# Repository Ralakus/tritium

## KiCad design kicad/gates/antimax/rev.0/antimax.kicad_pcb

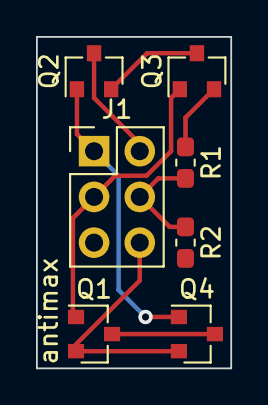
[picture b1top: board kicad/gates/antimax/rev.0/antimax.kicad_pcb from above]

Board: 2 copper layers, 10.8 x 18.4 mm, 7 parts (0 on the bottom side), 8 nets.

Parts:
J1: Conn_02x03_Odd_Even; PinHeader_2x03_P2.54mm_Vertical
Q1, Q4: 2N7002; SOT-23
Q2, Q3: BSS84; SOT-23
R1, R2: 12k; R_0603_1608Metric_Pad1.05x0.95mm_HandSolder

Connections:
A: J1.1, Q2.1, Q4.1
B: J1.3, Q1.1, Q3.1
unnamed: Q1.3, Q4.3, R2.2
unnamed: Q2.2, Q3.3
unnamed: Q3.2, R1.1
Out: J1.4, R1.2, R2.1
Vdd: J1.2, Q2.3
Vss: J1.6, Q1.2, Q4.2

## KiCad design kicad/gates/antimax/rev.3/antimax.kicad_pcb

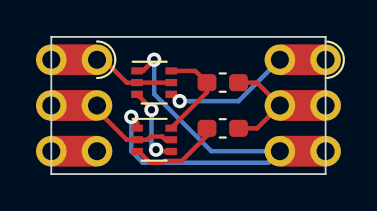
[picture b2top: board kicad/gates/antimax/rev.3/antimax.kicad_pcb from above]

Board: 2 copper layers, 15.2 x 7.6 mm, 6 parts (0 on the bottom side), 8 nets.

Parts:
J1, J2: Conn_01x03; Hybrid_Castellation_1x03_P2.54
Q1, Q2: BSS8402DW; SOT-363_SC-70-6
R1, R2: 12k; R_0603_1608Metric_Pad1.05x0.95mm_HandSolder

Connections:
A: J1.1, Q1.2, Q1.5
B: J1.2, Q2.2, Q2.5
unnamed: Q1.3, Q2.4
unnamed: Q1.6, Q2.6, R2.2
unnamed: Q2.3, R1.1
Out: J2.2, R1.2, R2.1
Vdd: J2.1, Q1.4
Vss: J2.3, Q1.1, Q2.1

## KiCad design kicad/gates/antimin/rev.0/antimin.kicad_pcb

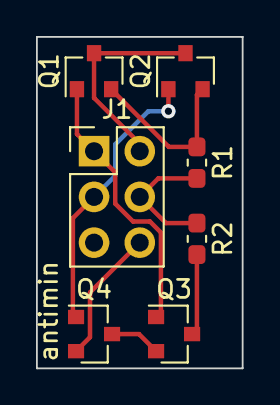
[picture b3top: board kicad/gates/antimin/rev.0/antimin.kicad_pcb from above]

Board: 2 copper layers, 11.4 x 18.4 mm, 7 parts (0 on the bottom side), 8 nets.

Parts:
J1: Conn_02x03_Odd_Even; PinHeader_2x03_P2.54mm_Vertical
Q1, Q2: BSS84; SOT-23
Q3, Q4: 2N7002E; SOT-23
R1, R2: 12k; R_0603_1608Metric_Pad1.05x0.95mm_HandSolder

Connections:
A: J1.1, Q1.1, Q3.1
B: J1.3, Q2.1, Q4.1
unnamed: Q1.2, Q2.2, R1.1
unnamed: Q3.2, Q4.3
unnamed: Q3.3, R2.2
Out: J1.4, R1.2, R2.1
Vdd: J1.2, Q1.3, Q2.3
Vss: J1.6, Q4.2

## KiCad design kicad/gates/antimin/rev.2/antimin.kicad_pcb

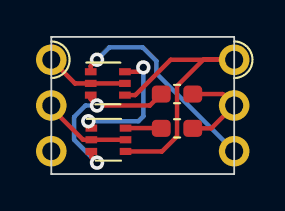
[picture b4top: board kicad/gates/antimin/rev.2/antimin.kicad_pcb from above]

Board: 2 copper layers, 10.2 x 7.6 mm, 6 parts (0 on the bottom side), 8 nets.

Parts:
J1, J2: Conn_01x03; Edge_Castellation_1x03_P2.54
Q1, Q2: BSS8402DW; SOT-363_SC-70-6
R1, R2: 12k; R_0603_1608Metric_Pad1.05x0.95mm_HandSolder

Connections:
A: J1.1, Q1.2, Q1.5
B: J1.2, Q2.2, Q2.5
unnamed: Q1.3, Q2.3, R1.1
unnamed: Q1.6, Q2.1
unnamed: Q2.6, R2.2
Out: J2.2, R1.2, R2.1
Vdd: J2.1, Q1.4, Q2.4
Vss: J2.3, Q1.1
